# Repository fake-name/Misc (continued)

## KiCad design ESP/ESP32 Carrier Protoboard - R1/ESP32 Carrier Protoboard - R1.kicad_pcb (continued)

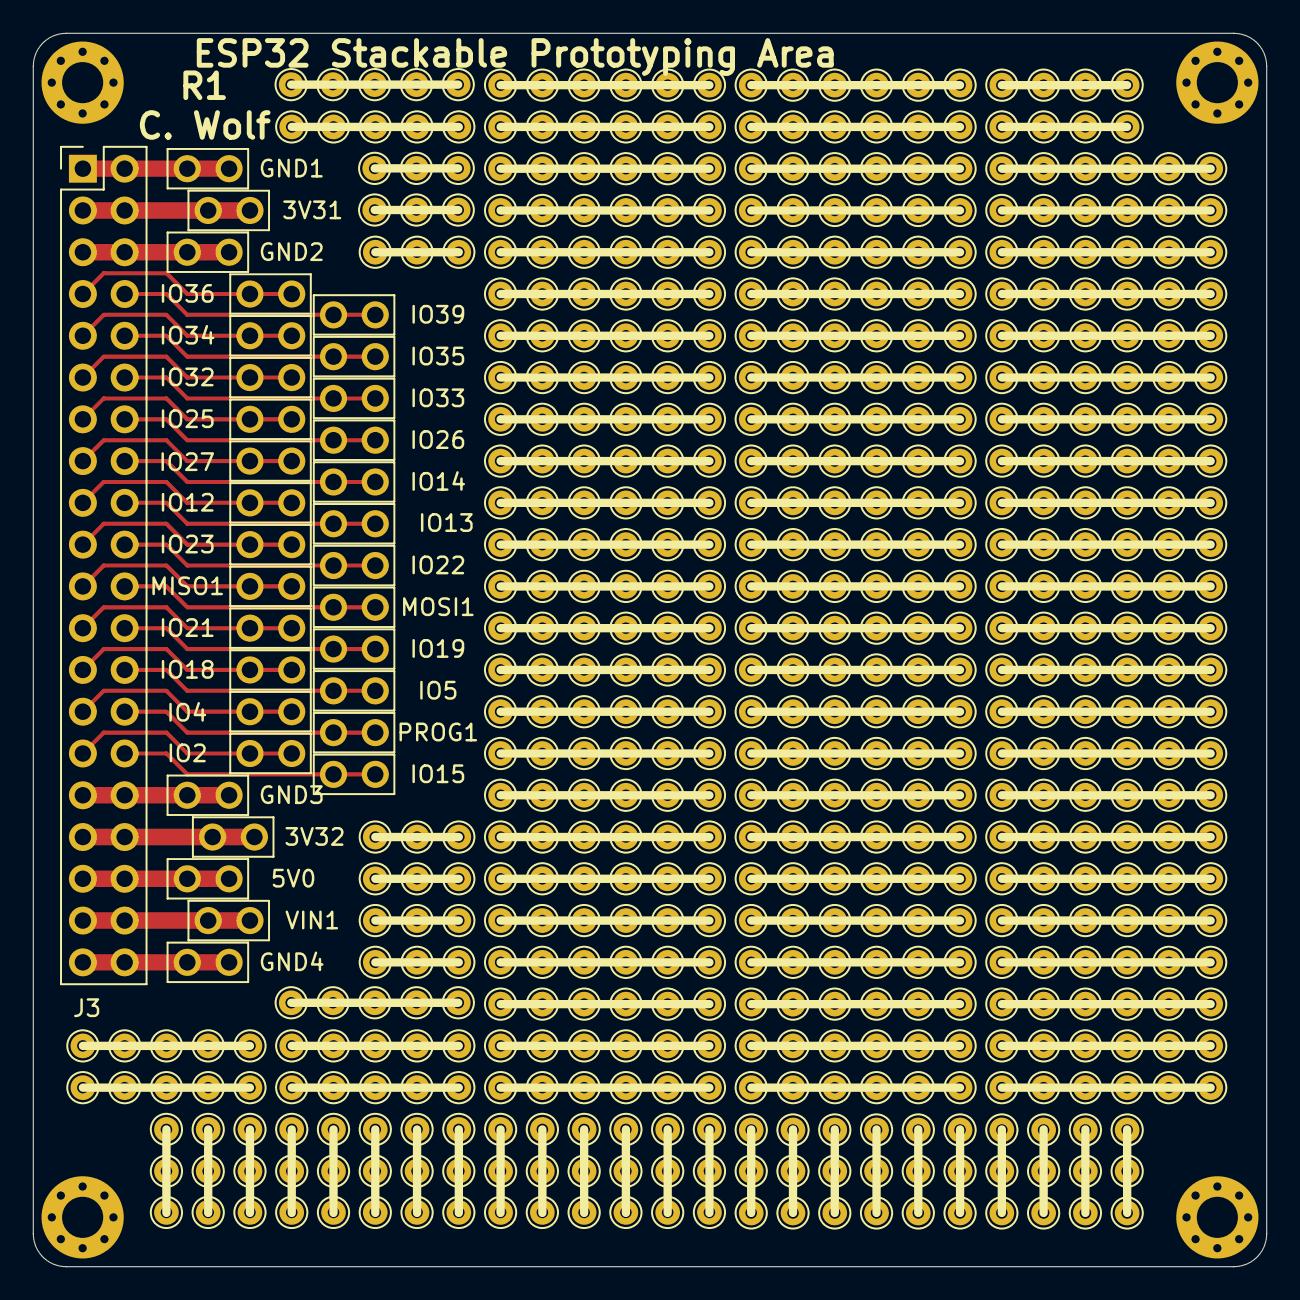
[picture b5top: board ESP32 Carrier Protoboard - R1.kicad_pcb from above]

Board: 2 copper layers, 75.0 x 75.0 mm, 37 parts (0 on the bottom side), 28 nets.

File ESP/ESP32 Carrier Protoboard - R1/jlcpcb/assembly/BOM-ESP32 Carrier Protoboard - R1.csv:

Comment,Designator,Footprint,LCSC
TestPoint,IO2,TestPoint_Bridge_Pitch2.54mm_Drill1.0mm,
TestPoint,PROG1,TestPoint_Bridge_Pitch2.54mm_Drill1.0mm,
TestPoint,IO39,TestPoint_Bridge_Pitch2.54mm_Drill1.0mm,
TestPoint,VIN1,TestPoint_Bridge_Pitch2.54mm_Drill1.0mm,
TestPoint,GND4,TestPoint_Bridge_Pitch2.54mm_Drill1.0mm,
TestPoint,GND3,TestPoint_Bridge_Pitch2.54mm_Drill1.0mm,
TestPoint,GND2,TestPoint_Bridge_Pitch2.54mm_Drill1.0mm,
TestPoint,GND1,TestPoint_Bridge_Pitch2.54mm_Drill1.0mm,
TestPoint,5V0,TestPoint_Bridge_Pitch2.54mm_Drill1.0mm,
TestPoint,3V32,TestPoint_Bridge_Pitch2.54mm_Drill1.0mm,
TestPoint,3V31,TestPoint_Bridge_Pitch2.54mm_Drill1.0mm,
TestPoint,MOSI1,TestPoint_Bridge_Pitch2.54mm_Drill1.0mm,
TestPoint,MISO1,TestPoint_Bridge_Pitch2.54mm_Drill1.0mm,
TestPoint,IO36,TestPoint_Bridge_Pitch2.54mm_Drill1.0mm,
TestPoint,IO35,TestPoint_Bridge_Pitch2.54mm_Drill1.0mm,
TestPoint,IO34,TestPoint_Bridge_Pitch2.54mm_Drill1.0mm,
TestPoint,IO33,TestPoint_Bridge_Pitch2.54mm_Drill1.0mm,
TestPoint,IO32,TestPoint_Bridge_Pitch2.54mm_Drill1.0mm,
TestPoint,IO27,TestPoint_Bridge_Pitch2.54mm_Drill1.0mm,
TestPoint,IO26,TestPoint_Bridge_Pitch2.54mm_Drill1.0mm,
TestPoint,IO25,TestPoint_Bridge_Pitch2.54mm_Drill1.0mm,
TestPoint,IO23,TestPoint_Bridge_Pitch2.54mm_Drill1.0mm,
TestPoint,IO22,TestPoint_Bridge_Pitch2.54mm_Drill1.0mm,
TestPoint,IO21,TestPoint_Bridge_Pitch2.54mm_Drill1.0mm,
TestPoint,IO19,TestPoint_Bridge_Pitch2.54mm_Drill1.0mm,
TestPoint,IO18,TestPoint_Bridge_Pitch2.54mm_Drill1.0mm,
TestPoint,IO15,TestPoint_Bridge_Pitch2.54mm_Drill1.0mm,
TestPoint,IO14,TestPoint_Bridge_Pitch2.54mm_Drill1.0mm,
TestPoint,IO13,TestPoint_Bridge_Pitch2.54mm_Drill1.0mm,
TestPoint,IO12,TestPoint_Bridge_Pitch2.54mm_Drill1.0mm,
TestPoint,IO5,TestPoint_Bridge_Pitch2.54mm_Drill1.0mm,
TestPoint,IO4,TestPoint_Bridge_Pitch2.54mm_Drill1.0mm,
MountingHole,H3,MountingHole_2.5mm_Pad_Via,
MountingHole,H4,MountingHole_2.5mm_Pad_Via,
MountingHole,H2,MountingHole_2.5mm_Pad_Via,
MountingHole,H1,MountingHole_2.5mm_Pad_Via,
ESP32-DevBoard-Header,J3,PinHeader_2x20_P2.54mm_Vertical,

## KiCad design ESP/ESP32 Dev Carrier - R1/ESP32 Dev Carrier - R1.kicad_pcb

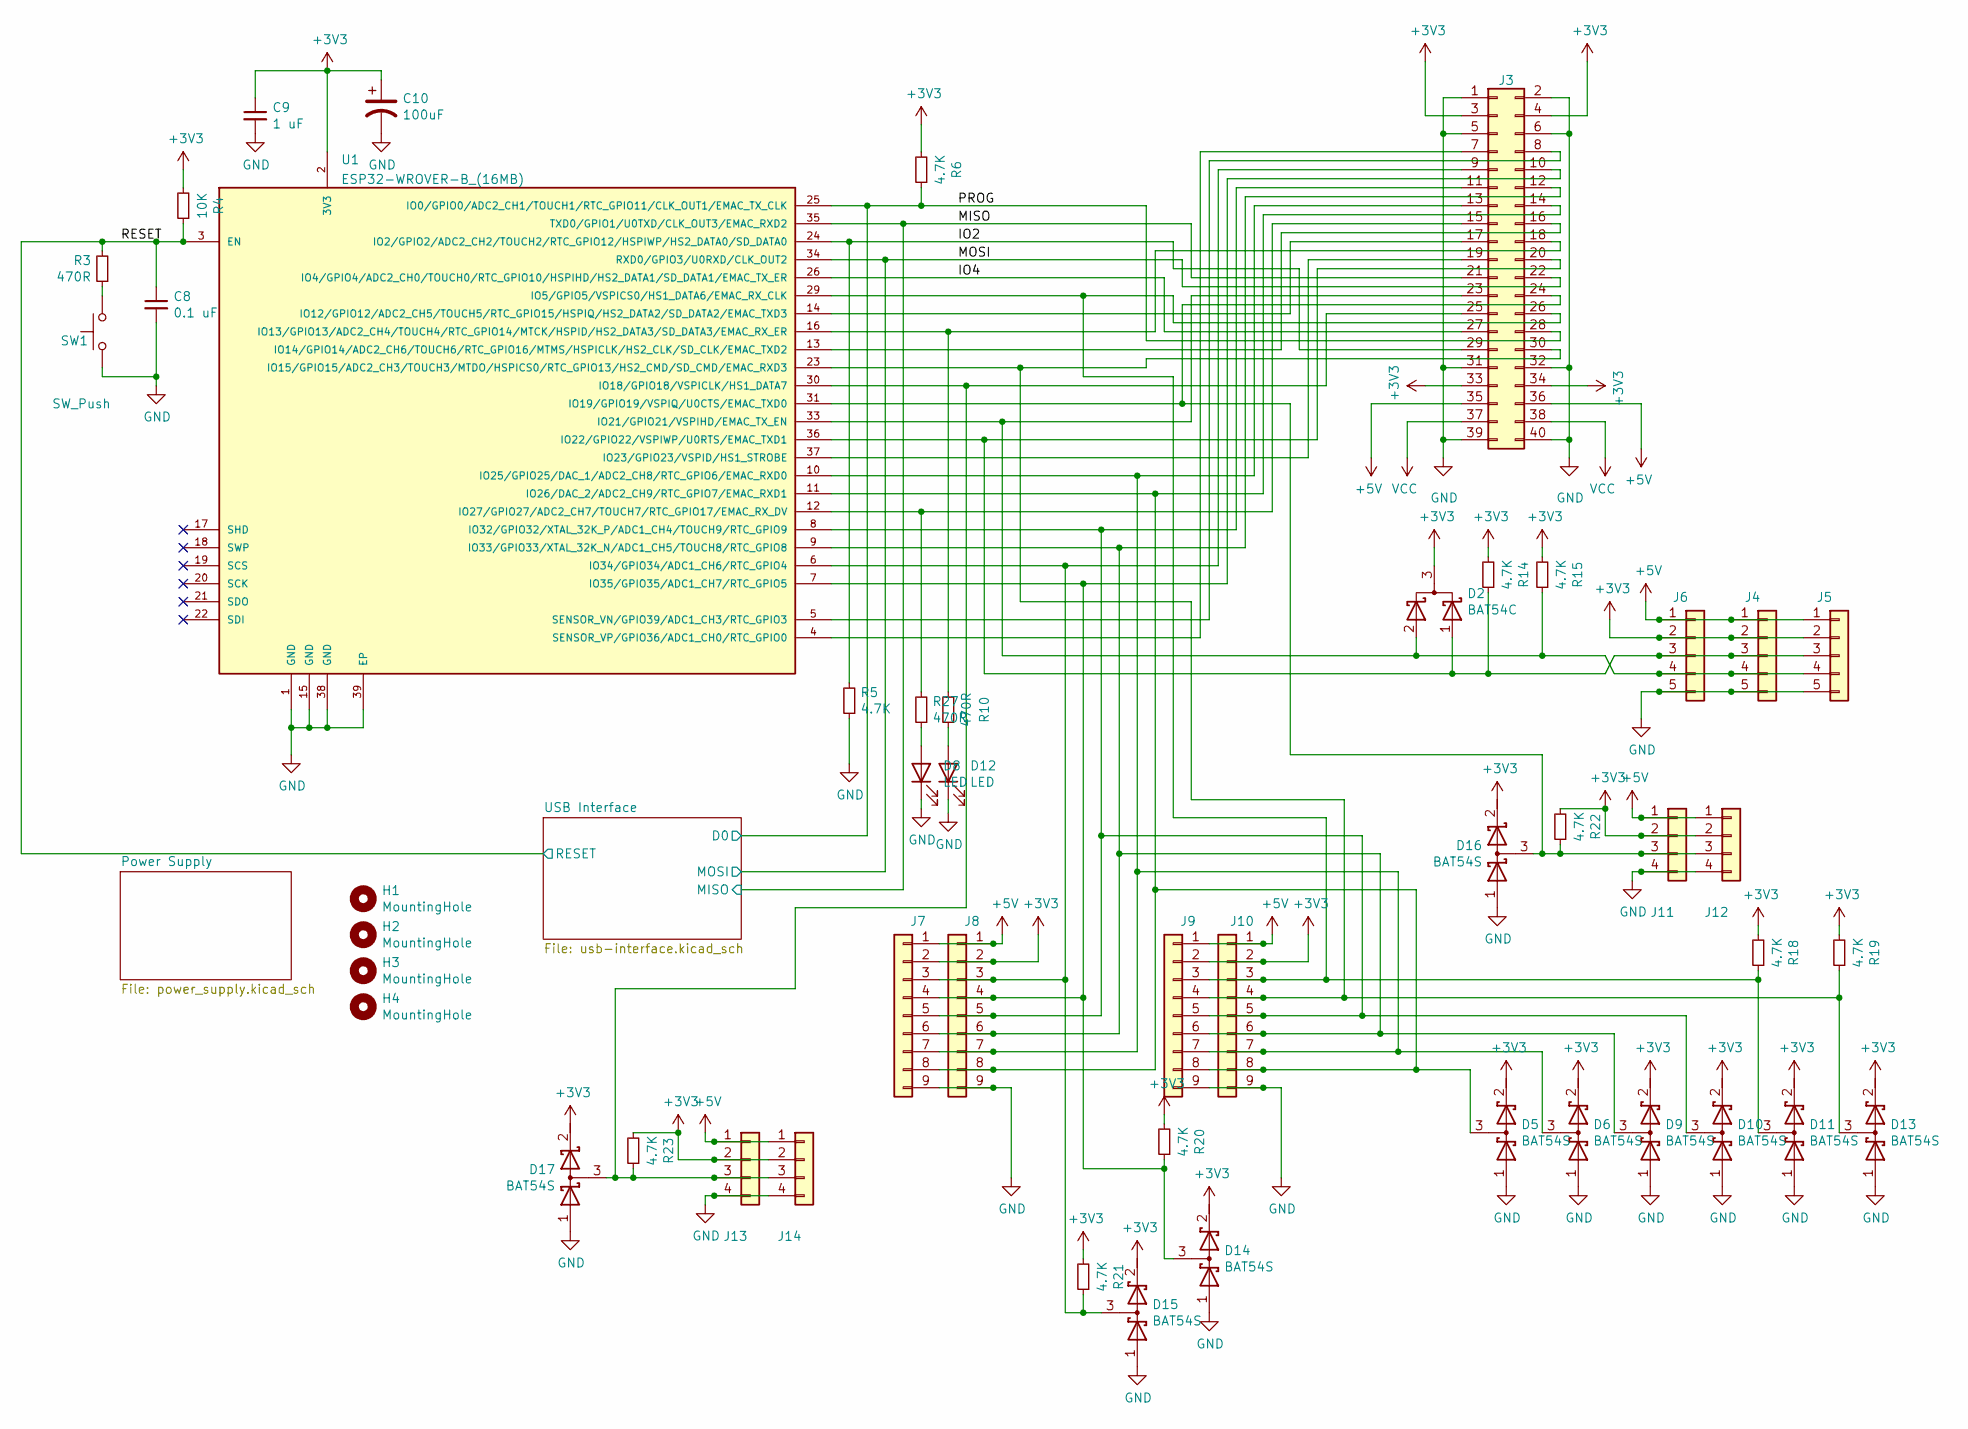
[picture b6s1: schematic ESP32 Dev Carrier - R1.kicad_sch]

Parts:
C8: 0.1 uF; C_0603_1608Metric; LCSC C15849
C9: 1 uF; C_0603_1608Metric; LCSC C14663
C10: 100uF; CP_EIA-7343-20_Kemet-V; LCSC C14663
D2: BAT54C; SOT-23; LCSC C14663
D5, D6, D9, D10, D11, D13, D14, D15, D16, D17: BAT54S; SOT-23
D8, D12: LED; CHIPLED_0603; LCSC C14663
H1, H2, H3, H4: MountingHole; MountingHole_2.5mm_Pad_Via
J3: Conn_02x20_Top_Bottom; PinHeader_2x20_P2.54mm_Vertical
J4, J5, J6: Conn_01x05; JST_XH_B5B-XH-A_1x05_P2.50mm_Vertical; LCSC C14663
J7, J8, J9, J10: Conn_01x09; JST_XH_B9B-XH-A_1x09_P2.50mm_Vertical
J11, J12, J13, J14: Conn_01x04; JST_XH_B4B-XH-A_1x04_P2.50mm_Vertical
R3, R10, R27: 470R; R_0603_1608Metric; LCSC C14663
R4: 10K; R_0603_1608Metric; LCSC C14663
R5, R6, R14, R15: 4.7K; R_0603_1608Metric; LCSC C14663
R18, R19, R20, R21, R22, R23: 4.7K; R_0603_1608Metric
SW1: SW_Push; SW_SPST_CK_RS282G05A3; LCSC C14663
U1: ESP32-WROVER-B_(16MB); XCVR_ESP32-WROVER-B_(16MB); PARTREV 1.1

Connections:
+3V3: C9.1, C10.1, D2.3 (A), D5.2 (K), D6.2 (K), D9.2 (K), D10.2 (K), D11.2 (K), D13.2 (K), D14.2 (K), D15.2 (K), D16.2 (K), D17.2 (K), J3.3, J3.4, J3.33, J3.34, J4.2, J5.2, J6.2, J7.2, J8.2, J9.2, J10.2, J11.2, J12.2, J13.2, J14.2, R4.2, R6.2, R14.2, R15.2, R18.2, R19.2, R20.2, R21.2, R22.2, R23.2, U1.2 (3V3); also elsewhere on the board
+5V: J3.35, J3.36, J4.1, J5.1, J6.1, J7.1, J8.1, J9.1, J10.1, J11.1, J12.1, J13.1, J14.1; also elsewhere on the board
/IO2: J3.29, R5.2, U1.24 (IO2/GPIO2/ADC2_CH2/TOUCH2/RTC_GPIO12/HS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)
/IO4: J3.27, U1.26 (IO4/GPIO4/ADC2_CH0/TOUCH0/RTC_GPIO10/HS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)
/MISO: J3.21, U1.35 (TXD0/GPIO1/U0TXD/CLK_OUT3/EMAC_RXD2); also elsewhere on the board
/MOSI: J3.22, U1.34 (RXD0/GPIO3/U0RXD/CLK_OUT2); also elsewhere on the board
/PROG: J3.28, R6.1, U1.25 (IO0/GPIO0/ADC2_CH1/TOUCH1/RTC_GPIO11/CL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); also elsewhere on the board
/RESET: C8.1, R3.2, R4.1, U1.3 (EN); also elsewhere on the board
GND: C8.2, C9.2, C10.2, D5.1 (A), D6.1 (A), D8.1 (K), D9.1 (A), D10.1 (A), D11.1 (A), D12.1 (K), D13.1 (A), D14.1 (A), D15.1 (A), D16.1 (A), D17.1 (A), J3.1, J3.2, J3.5, J3.6, J3.31, J3.32, J3.39, J3.40, J4.5, J5.5, J6.5, J7.9, J8.9, J9.9, J10.9, J11.4, J12.4, J13.4, J14.4, R5.1, SW1.2, U1.1 (GND), U1.15 (GND), U1.38 (GND), U1.39 (EP); also elsewhere on the board
unnamed: D2.1 (K), J3.20, J4.3, J5.3, J6.3, R14.1, U1.36 (IO22/GPIO22/VSPIWP/U0RTS/EMAC_TXD1)
unnamed: D2.2 (K), J3.23, J4.4, J5.4, J6.4, R15.1, U1.33 (IO21/GPIO21/VSPIHD/EMAC_TX_EN)
unnamed: D5.3 (common), J3.14, J7.8, J8.8, J9.8, J10.8, U1.11 (IO26/DAC_2/ADC2_CH9/RTC_GPIO7/EMAC_RXD1)
unnamed: D6.3 (common), J3.13, J7.7, J8.7, J9.7, J10.7, U1.10 (IO25/GPIO25/DAC_1/ADC2_CH8/RTC_GPIO6/EM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)
unnamed: D8.2 (A), R27.1
unnamed: D9.3 (common), J3.12, J7.6, J8.6, J9.6, J10.6, U1.9 (IO33/GPIO33/XTAL_32K_N/ADC1_CH5/TOUCH8/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)
unnamed: D10.3 (common), J3.11, J7.5, J8.5, J9.5, J10.5, U1.8 (IO32/GPIO32/XTAL_32K_P/ADC1_CH4/TOUCH9/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)
unnamed: D11.3 (common), J3.26, J9.3, J10.3, R18.1, U1.29 (IO5/GPIO5/VSPICS0/HS1_DATA6/EMAC_RX_CLK)
unnamed: D12.2 (A), R10.1
unnamed: D13.3 (common), J3.30, J9.4, J10.4, R19.1, U1.23 (IO15/GPIO15/ADC2_CH3/TOUCH3/MTDO/HSPICS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)
unnamed: D14.3 (common), J3.10, J7.4, J8.4, R20.1, U1.7 (IO35/GPIO35/ADC1_CH7/RTC_GPIO5)
unnamed: D15.3 (common), J3.9, J7.3, J8.3, R21.1, U1.6 (IO34/GPIO34/ADC1_CH6/RTC_GPIO4)
unnamed: D16.3 (common), J3.24, J11.3, J12.3, R22.1, U1.31 (IO19/GPIO19/VSPIQ/U0CTS/EMAC_TXD0)
unnamed: D17.3 (common), J3.25, J13.3, J14.3, R23.1, U1.30 (IO18/GPIO18/VSPICLK/HS1_DATA7)
unnamed: J3.7, U1.4 (SENSOR_VP/GPIO36/ADC1_CH0/RTC_GPIO0)
unnamed: J3.8, U1.5 (SENSOR_VN/GPIO39/ADC1_CH3/RTC_GPIO3)
unnamed: J3.15, R27.2, U1.12 (IO27/GPIO27/ADC2_CH7/TOUCH7/RTC_GPIO17/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)
unnamed: J3.16, U1.13 (IO14/GPIO14/ADC2_CH6/TOUCH6/RTC_GPIO16/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)
unnamed: J3.17, U1.14 (IO12/GPIO12/ADC2_CH5/TOUCH5/RTC_GPIO15/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)
unnamed: J3.18, R10.2, U1.16 (IO13/GPIO13/ADC2_CH4/TOUCH4/RTC_GPIO14/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)
unnamed: J3.19, U1.37 (IO23/GPIO23/VSPID/HS1_STROBE)
unnamed: R3.1, SW1.1
VCC: J3.37, J3.38; also elsewhere on the board

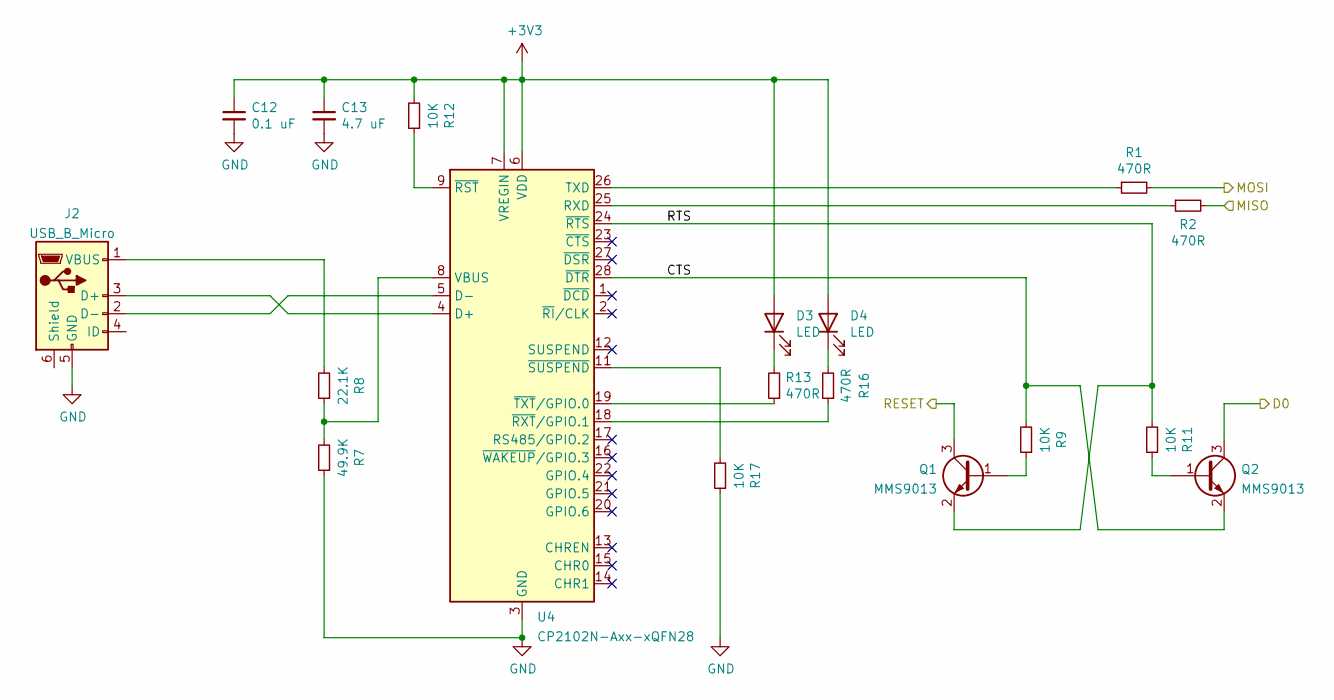
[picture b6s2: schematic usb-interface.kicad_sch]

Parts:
C12: 0.1 uF; C_0603_1608Metric; LCSC C14663
C13: 4.7 uF; C_0603_1608Metric; LCSC C19666
D3, D4: LED; CHIPLED_0603; LCSC C14663
J2: USB_B_Micro; Molex--0-0-0
Q1, Q2: MMS9013; SOT-23; LCSC MMS9013
R1, R2, R13, R16: 470R; R_0603_1608Metric; LCSC C14663
R7: 49.9K; R_0603_1608Metric; LCSC C23184
R8: 22.1K; R_0603_1608Metric; LCSC C23184
R9, R11, R12, R17: 10K; R_0603_1608Metric; LCSC C25804
U4: CP2102N-Axx-xQFN28; QFN-28-1EP_5x5mm_P0.5mm_EP3.35x3.35mm

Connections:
+3V3: C12.1, C13.1, D3.2 (A), D4.2 (A), R12.2, U4.6 (VDD), U4.7 (VREGIN); also elsewhere on the board
/MISO: R2.2; also elsewhere on the board
/MOSI: R1.2; also elsewhere on the board
/PROG: Q2.3 (C); also elsewhere on the board
/RESET: Q1.3 (C); also elsewhere on the board
/USB Interface/CTS: Q2.2 (E), R9.2, U4.28 (~DTR)
/USB Interface/RTS: Q1.2 (E), R11.2, U4.24 (~RTS)
GND: C12.2, C13.2, J2.5 (GND), R7.1, R17.1, U4.3 (GND), U4.29 (GND); also elsewhere on the board
unnamed: D3.1 (K), R13.2
unnamed: D4.1 (K), R16.2
unnamed: J2.1 (VBUS), R8.2
unnamed: J2.2 (D-), U4.5 (D-)
unnamed: J2.3 (D+), U4.4 (D+)
unnamed: Q1.1 (B), R9.1
unnamed: Q2.1 (B), R11.1
unnamed: R1.1, U4.26 (TXD)
unnamed: R2.1, U4.25 (RXD)
unnamed: R7.2, R8.1, U4.8 (VBUS)
unnamed: R12.1, U4.9 (~RST)
unnamed: R13.1, U4.19 (~TXT/GPIO.0)
unnamed: R16.1, U4.18 (~RXT/GPIO.1)
unnamed: R17.2, U4.11 (~SUSPEND)

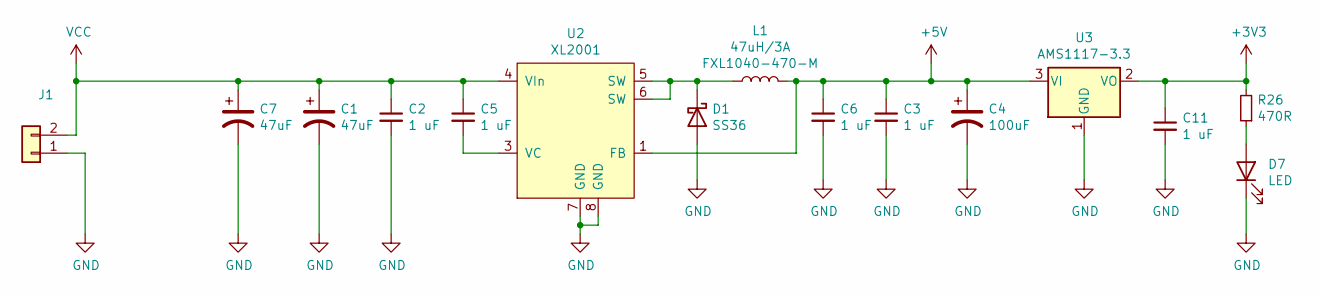
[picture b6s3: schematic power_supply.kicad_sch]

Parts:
C1: 47uF; CP_Radial_D6.3mm_P2.50mm; LCSC C14663
C2: 1 uF; C_1206_3216Metric; LCSC C14663
C3, C5, C6, C11: 1 uF; C_0603_1608Metric; LCSC C14663
C4: 100uF; CP_EIA-7343-20_Kemet-V; LCSC C14663
C7: 47uF; CP_EIA-7343-20_Kemet-V; LCSC C14663
D1: SS36; D_SMA; LCSC C14663
D7: LED; CHIPLED_0603; LCSC C14663
J1: Conn_01x02; JST_XH_B2B-XH-AM_1x02_P2.50mm_Vertical; LCSC C14663
L1: 47uH/3A; L_Wuerth_HCI-1040; LCSC C14663
R26: 470R; R_0603_1608Metric; LCSC C14663
U2: XL2001; SOIC-8_3.9x4.9mm_P1.27mm; LCSC C14663
U3: AMS1117-3.3; SOT-223-3_TabPin2; LCSC C14663

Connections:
+3V3: C11.1, R26.2, U3.2 (VO); also elsewhere on the board
+5V: C3.1, C4.1, C6.1, L1.2, U2.1 (FB), U3.3 (VI); also elsewhere on the board
GND: C1.2, C2.2, C3.2, C4.2, C6.2, C7.2, C11.2, D1.2 (A), D7.1 (K), J1.1, U2.7 (GND), U2.8 (GND), U3.1 (GND); also elsewhere on the board
unnamed: C5.2, U2.3 (VC)
unnamed: D1.1 (K), L1.1, U2.5 (SW), U2.6 (SW)
unnamed: D7.2 (A), R26.1
VCC: C1.1, C2.1, C5.1, C7.1, J1.2, U2.4 (VIn); also elsewhere on the board

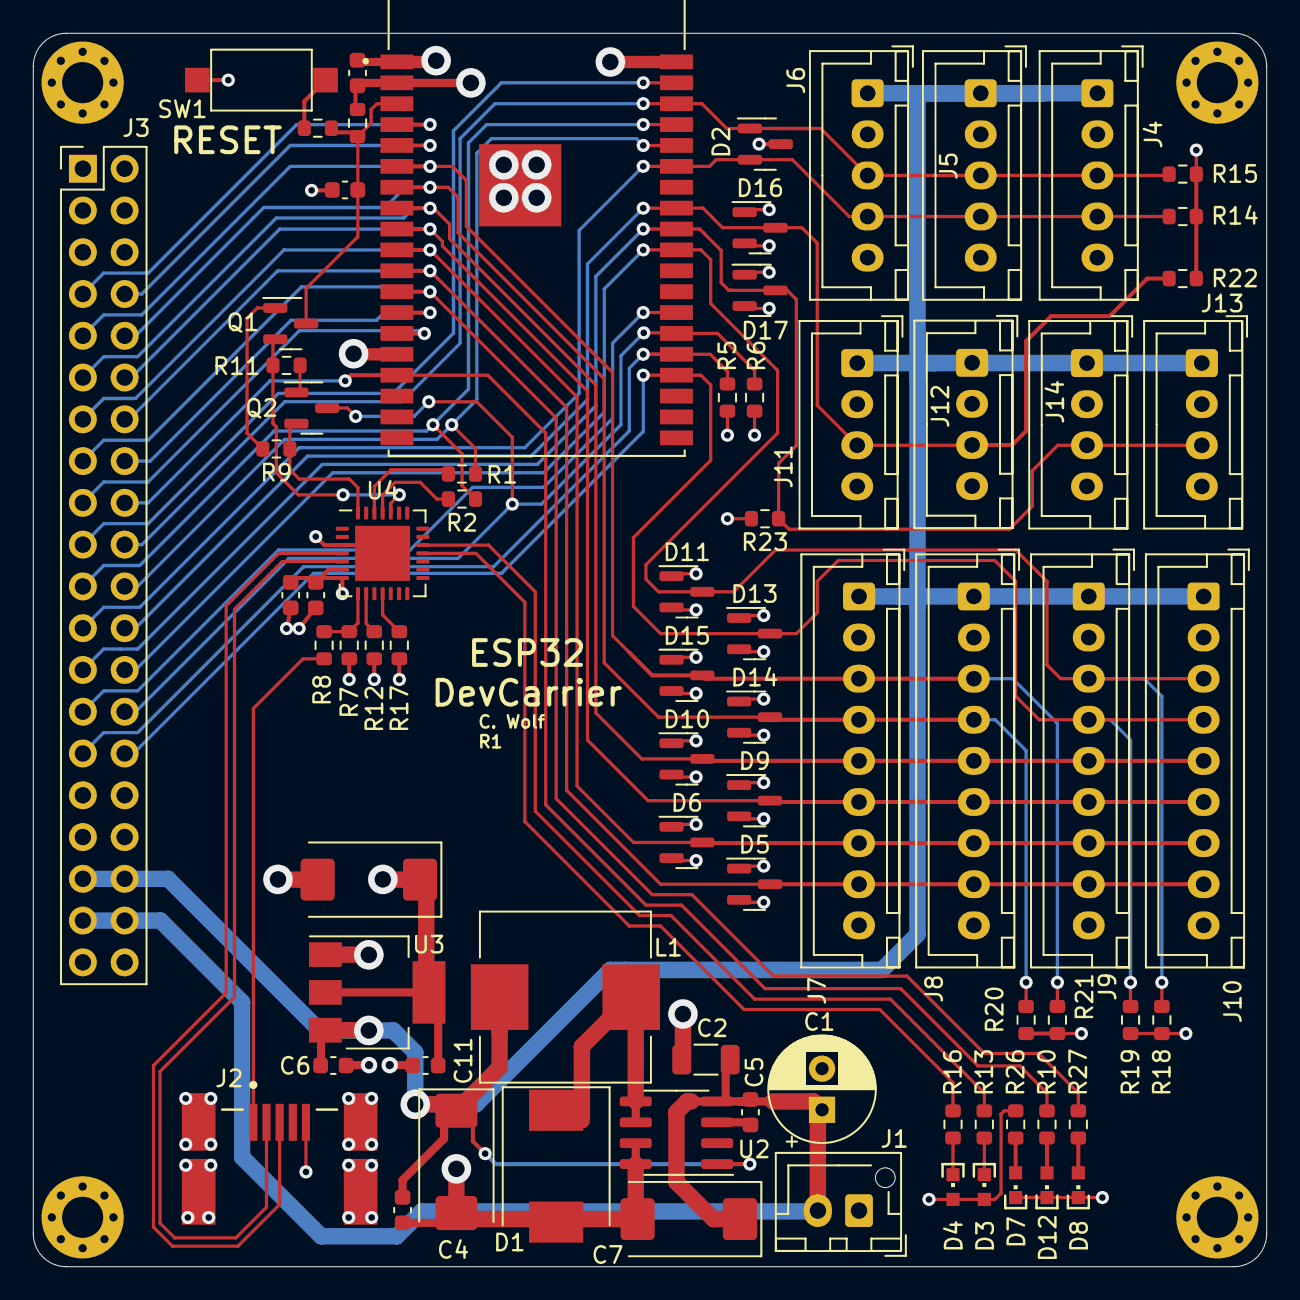
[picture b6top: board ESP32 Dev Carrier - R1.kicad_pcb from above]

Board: 4 copper layers, 75.0 x 75.0 mm, 81 parts (0 on the bottom side), 51 nets.

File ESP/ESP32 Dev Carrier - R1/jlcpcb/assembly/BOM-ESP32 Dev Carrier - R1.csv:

Comment,Designator,Footprint,LCSC
USB_B_Micro,J2,Molex--0-0-0,C136452
47uF,"C1,C12,C8,J1,J4,J5,J6",CP_Radial_D6.3mm_P2.50mm,C14663
100uF,"C10,C4",CP_EIA-7343-20_Kemet-V,C155463
1 uF,"C11,C3,C5,C6,C9",C_0603_1608Metric,C15849
LED,"D12,D3,D4,D7,D8",CHIPLED_0603,C165982
1 uF,C2,C_1206_3216Metric,C1848
4.7 uF,C13,C_0603_1608Metric,C19666
4.7K,"R14,R15,R18,R19,R20,R21,R22,R23,R5,R6",R_0603_1608Metric,C23162
470R,"R1,R10,R13,R16,R2,R26,R27,R3",R_0603_1608Metric,C23179
49.9K,"R7,R8",R_0603_1608Metric,C23184
10K,"R11,R12,R17,R4,R9",R_0603_1608Metric,C25804
ESP32-WROVER-B_(16MB),U1,XCVR_ESP32-WROVER-B_(16MB),"C2973667
"
SS36,D1,D_SMC,C35722
47uH/3A,L1,L_Wuerth_HCI-1040,C360726
BAT54S,"D10,D11,D13,D14,D15,D16,D17,D2,D5,D6,D9",SOT-23,C37704
SW_Push,SW1,SW_SPST_CK_RS282G05A3,C500065
AMS1117-3.3,U3,SOT-223-3_TabPin2,C6186
CP2102N-Axx-xQFN28,U4,QFN-28-1EP_5x5mm_P0.5mm_EP3.35x3.35mm,C6568
XL2001,U2,SOIC-8_3.9x4.9mm_P1.27mm,C73336
47uF,C7,CP_EIA-7343-20_Kemet-V,C87110
MMS9013,"Q1,Q2",SOT-23,C90160
MountingHole,H4,MountingHole_2.5mm_Pad_Via,
MountingHole,H3,MountingHole_2.5mm_Pad_Via,
MountingHole,H2,MountingHole_2.5mm_Pad_Via,
MountingHole,H1,MountingHole_2.5mm_Pad_Via,
Conn_01x09,J8,JST_XH_B9B-XH-A_1x09_P2.50mm_Vertical,
Conn_01x09,J9,JST_XH_B9B-XH-A_1x09_P2.50mm_Vertical,
Conn_02x20_Top_Bottom,J3,PinHeader_2x20_P2.54mm_Vertical,
Conn_01x04,J14,JST_XH_B4B-XH-A_1x04_P2.50mm_Vertical,
Conn_01x04,J13,JST_XH_B4B-XH-A_1x04_P2.50mm_Vertical,
Conn_01x09,J10,JST_XH_B9B-XH-A_1x09_P2.50mm_Vertical,
Conn_01x04,J11,JST_XH_B4B-XH-A_1x04_P2.50mm_Vertical,
Conn_01x09,J7,JST_XH_B9B-XH-A_1x09_P2.50mm_Vertical,
Conn_01x04,J12,JST_XH_B4B-XH-A_1x04_P2.50mm_Vertical,

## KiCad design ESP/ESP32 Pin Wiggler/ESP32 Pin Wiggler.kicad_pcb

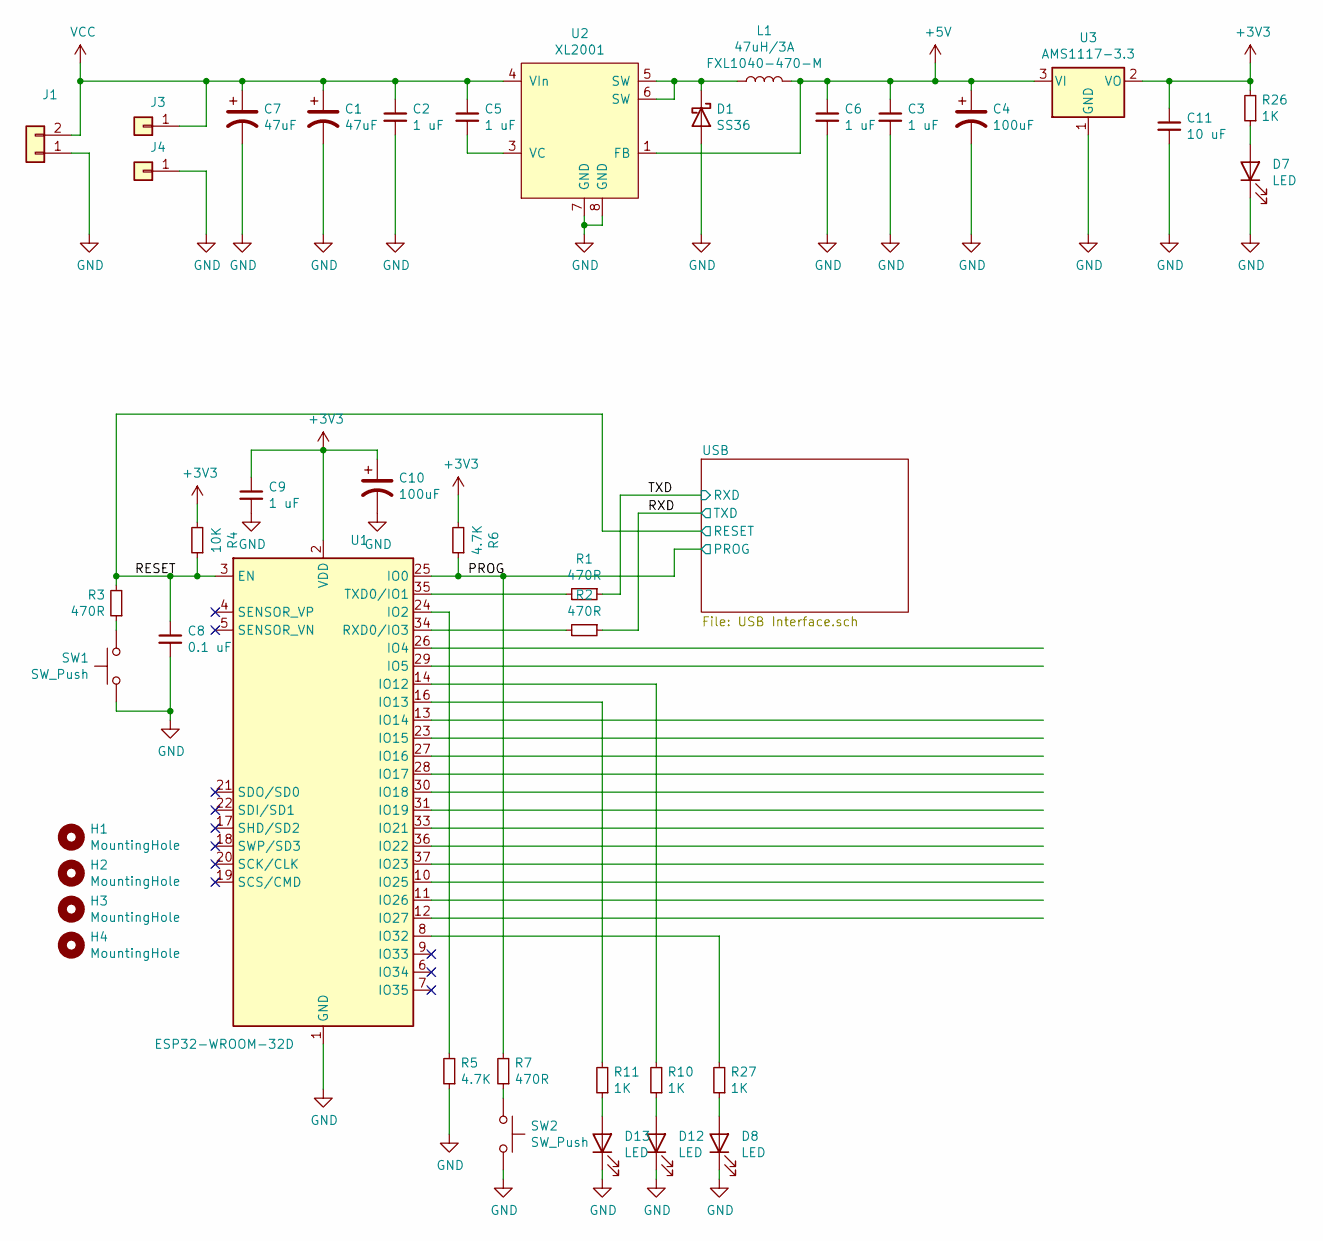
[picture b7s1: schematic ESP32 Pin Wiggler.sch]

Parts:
C1: 47uF; CP_Radial_D6.3mm_P2.50mm
C2: 1 uF; C_1206_3216Metric_Pad1.42x1.75mm_HandSolder
C3, C5, C6, C9: 1 uF; C_0603_1608Metric_Pad1.05x0.95mm_HandSolder
C4, C10: 100uF; CP_EIA-7343-20_Kemet-V_Pad2.25x2.55mm_HandSolder
C7: 47uF; CP_EIA-7343-20_Kemet-V_Pad2.25x2.55mm_HandSolder
C8: 0.1 uF; C_0603_1608Metric_Pad1.05x0.95mm_HandSolder
C11: 10 uF; C_0603_1608Metric_Pad1.05x0.95mm_HandSolder
D1: SS36; D_SMA_Handsoldering
D7, D8, D12, D13: LED; CHIPLED_0603
H1, H2, H3, H4: MountingHole; MountingHole_2.5mm_Pad_Via
J1: Conn_01x02; PinHeader_1x02_P2.54mm_Vertical
J3, J4: Conn_01x01; Pin_D1.3mm_L11.0mm
L1: 47uH/3A; L_Wuerth_HCI-1040
R1, R2, R3, R7: 470R; R_0603_1608Metric_Pad1.05x0.95mm_HandSolder
R4: 10K; R_0603_1608Metric_Pad1.05x0.95mm_HandSolder
R5, R6: 4.7K; R_0603_1608Metric_Pad1.05x0.95mm_HandSolder
R10, R11, R26, R27: 1K; R_0603_1608Metric_Pad1.05x0.95mm_HandSolder
SW1, SW2: SW_Push; K2-1823SA-A4DW-06
U1: ESP32-WROOM-32D; ESP32-WROOM-32
U2: XL2001; SOIC-8_3.9x4.9mm_P1.27mm
U3: AMS1117-3.3; SOT-223-3_TabPin2

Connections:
+3V3: C9.1, C10.1, C11.1, R4.2, R6.2, R26.2, U1.2 (VDD), U3.2 (VO); also elsewhere on the board
+5V: C3.1, C4.1, C6.1, L1.2, U2.1 (FB), U3.3 (VI)
/PROG: R6.1, R7.2, U1.25 (IO0); also elsewhere on the board
/RESET: C8.1, R3.2, R4.1, U1.3 (EN); also elsewhere on the board
/RXD: R2.1; also elsewhere on the board
/TXD: R1.1; also elsewhere on the board
GND: C1.2, C2.2, C3.2, C4.2, C6.2, C7.2, C8.2, C9.2, C10.2, C11.2, D1.2 (A), D7.1 (K), D8.1 (K), D12.1 (K), D13.1 (K), J1.1, J4.1, R5.1, SW1.2, SW2.2, U1.1 (GND), U1.15 (GND), U1.38 (GND), U1.39 (GND), U2.7 (GND), U2.8 (GND), U3.1 (GND); also elsewhere on the board
unnamed: C5.2, U2.3 (VC)
unnamed: D1.1 (K), L1.1, U2.5 (SW), U2.6 (SW)
unnamed: D7.2 (A), R26.1
unnamed: D8.2 (A), R27.1
unnamed: D12.2 (A), R10.1
unnamed: D13.2 (A), R11.1
unnamed: R1.2, U1.35 (TXD0/IO1)
unnamed: R2.2, U1.34 (RXD0/IO3)
unnamed: R3.1, SW1.1
unnamed: R5.2, U1.24 (IO2)
unnamed: R7.1, SW2.1
unnamed: R10.2, U1.14 (IO12)
unnamed: R11.2, U1.16 (IO13)
unnamed: R27.2, U1.8 (IO32)
VCC: C1.1, C2.1, C5.1, C7.1, J1.2, J3.1, U2.4 (VIn)

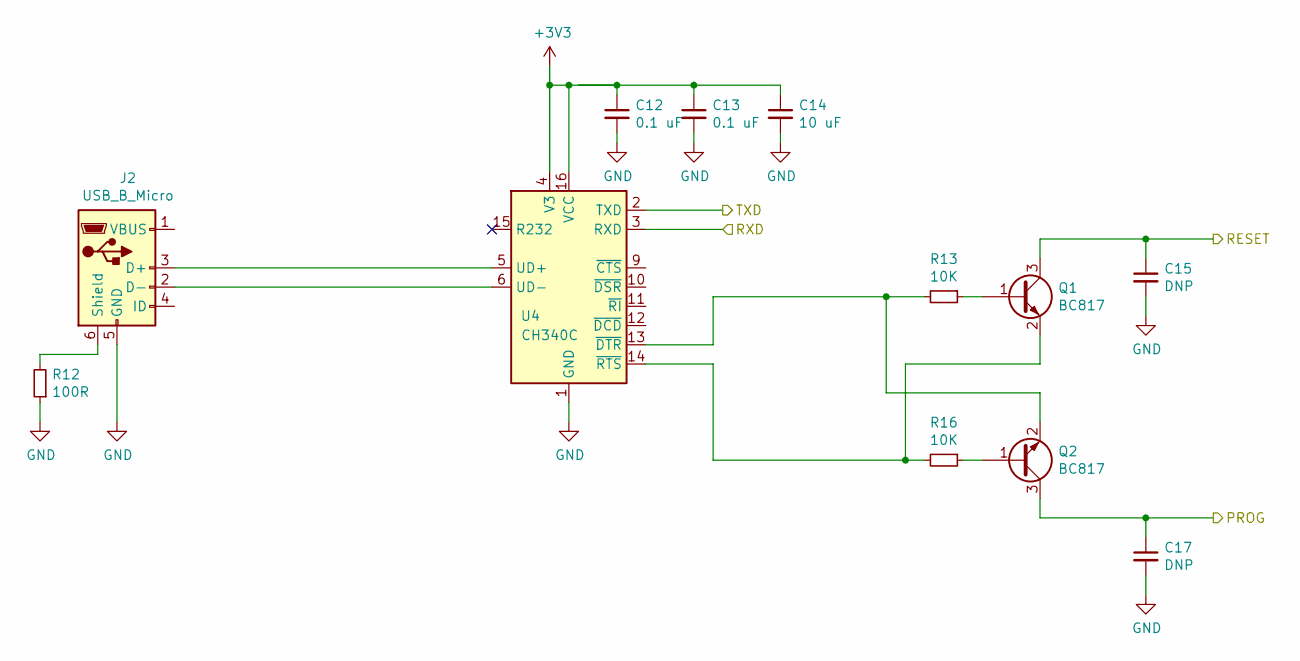
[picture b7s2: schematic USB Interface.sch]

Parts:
C12, C13: 0.1 uF; C_0603_1608Metric_Pad1.05x0.95mm_HandSolder
C14: 10 uF; C_0603_1608Metric_Pad1.05x0.95mm_HandSolder
C15, C17: DNP; C_0603_1608Metric_Pad1.05x0.95mm_HandSolder
J2: USB_B_Micro; USB_Micro-B_XKB_U254-051N-4BH806
Q1, Q2: BC817; SOT-23
R12: 100R; R_0603_1608Metric_Pad1.05x0.95mm_HandSolder
R13, R16: 10K; R_0603_1608Metric_Pad1.05x0.95mm_HandSolder
U4: CH340C; SOIC-16_3.9x9.9mm_P1.27mm

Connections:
+3V3: C12.1, C13.1, C14.1, U4.4 (V3), U4.16 (VCC); also elsewhere on the board
/PROG: C17.1, Q2.3 (C); also elsewhere on the board
/RESET: C15.1, Q1.3 (C); also elsewhere on the board
/RXD: U4.2 (TXD); also elsewhere on the board
/TXD: U4.3 (RXD); also elsewhere on the board
GND: C12.2, C13.2, C14.2, C15.2, C17.2, J2.5 (GND), R12.1, U4.1 (GND); also elsewhere on the board
unnamed: J2.2 (D-), U4.6 (UD-)
unnamed: J2.3 (D+), U4.5 (UD+)
unnamed: J2.6 (Shield), R12.2
unnamed: Q1.1 (B), R13.1
unnamed: Q1.2 (E), R16.2, U4.14 (~RTS)
unnamed: Q2.1 (B), R16.1
unnamed: Q2.2 (E), R13.2, U4.13 (~DTR)

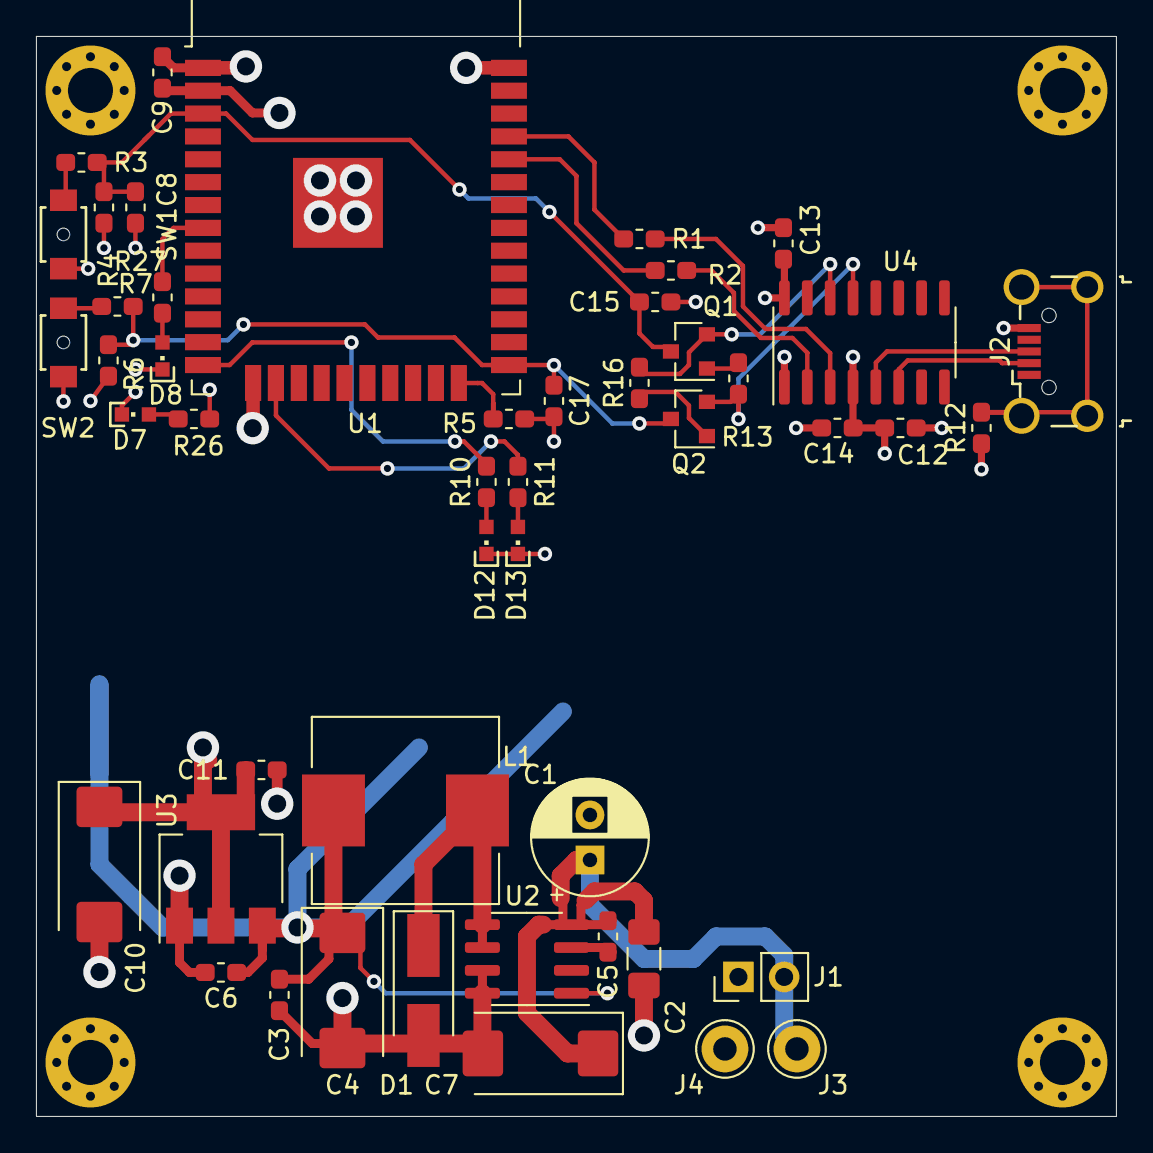
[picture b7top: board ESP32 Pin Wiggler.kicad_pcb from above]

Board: 4 copper layers, 60.0 x 60.0 mm, 52 parts (0 on the bottom side), 29 nets.
